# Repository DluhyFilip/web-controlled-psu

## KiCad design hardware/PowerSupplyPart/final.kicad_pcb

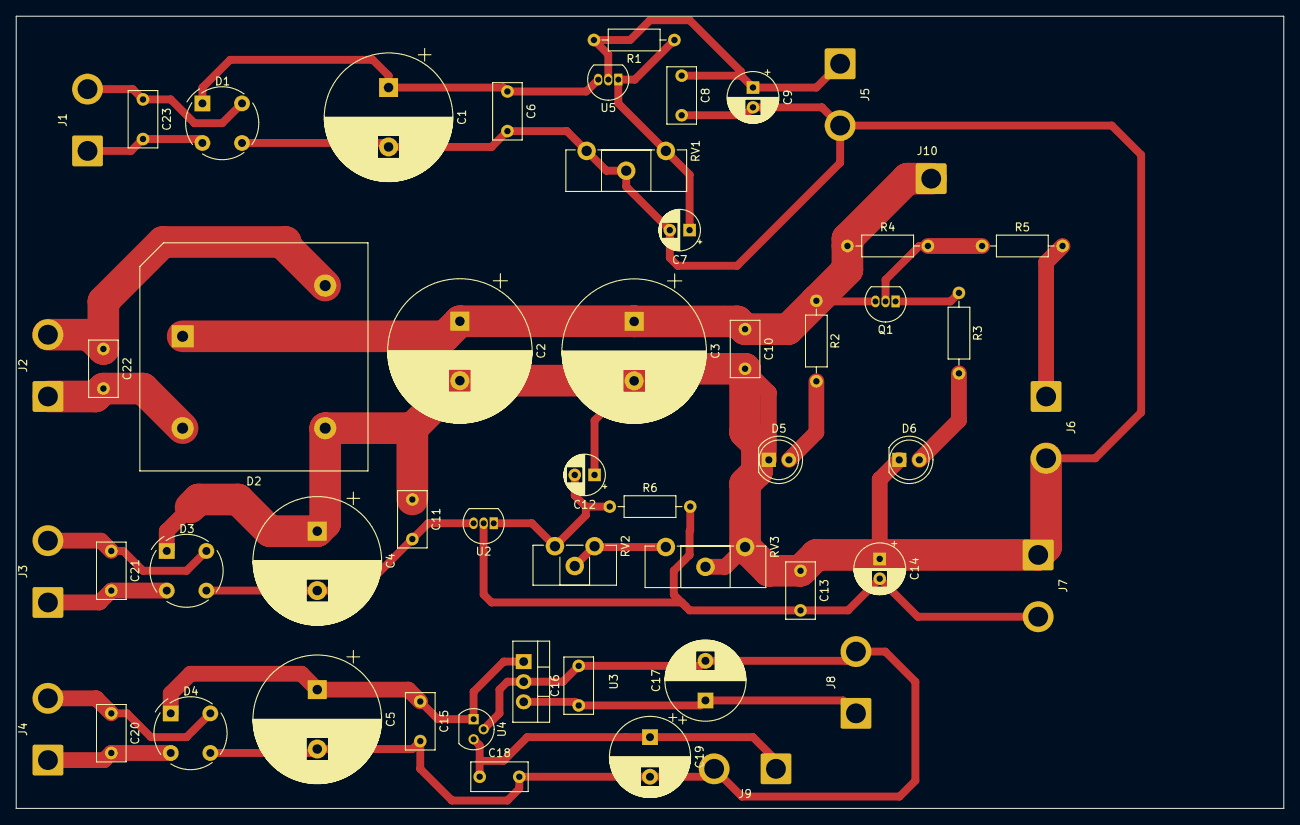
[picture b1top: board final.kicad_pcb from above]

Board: 2 copper layers, 160.0 x 100.0 mm, 53 parts (0 on the bottom side), 26 nets.

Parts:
C1, C4, C5: C_Polarized; CP_Radial_D16.0mm_P7.50mm
C2, C3: C_Polarized; CP_Radial_D18.0mm_P7.50mm
C6, C8, C10, C11, C13, C15, C16, C18, C20, C21, C22, C23: C; C_Rect_L7.0mm_W3.5mm_P5.00mm
C7: C; CP_Radial_D5.0mm_P2.50mm
C9, C14: C_Polarized; CP_Radial_D6.3mm_P2.50mm
C12: C_Polarized; CP_Radial_D5.0mm_P2.50mm
C17, C19: C_Polarized; CP_Radial_D10.0mm_P5.00mm
D1, D3, D4: D_Bridge_+A-A; Diode_Bridge_Round_D9.0mm
D2: D_Bridge_+A-A; Diode_Bridge_28.6x28.6x7.3mm_P18.0mm_P11.6mm
D5, D6: LED; LED_D5.0mm
J1, J2, J3, J4, J5, J6, J7, J8, J9: Conn_01x02_Socket; SolderWire-2sqmm_1x02_P7.8mm_D2mm_OD3.9mm
J10: Conn_01x01_Socket; SolderWire-2sqmm_1x01_D2mm_OD3.9mm
Q1: BC556; TO-92_Inline
R1, R2, R3, R4, R5, R6: R; R_Axial_DIN0207_L6.3mm_D2.5mm_P10.16mm_Horizontal
RV1, RV3: R_Potentiometer; Potentiometer_Piher_PT-15-H01_Horizontal
RV2: R_Potentiometer; Potentiometer_Piher_PT-10-H01_Horizontal
U2: LM337L_TO92; TO-92_Inline
U3: LM78M05_TO220; TO-220-3_Vertical
U4: L7805; TO-92
U5: LM317L_TO92; TO-92_Inline

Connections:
unnamed: C1.1, C6.1, D1.1 (+), U5.3 (VI)
unnamed: C1.2, C2.2, C3.2, C4.1, C6.2, C7.2, C8.2, C9.2, C10.2, C11.1, C12.1, C13.1, C14.1, D1.3 (-), D2.3 (-), D3.1 (+), D5.1 (K), D6.1 (K), J5.2, J6.2, J7.1, RV1.2, RV1.3, RV3.1, RV3.2
unnamed: C2.1, C3.1, C10.1, D2.1 (+), J10.1, Q1.3 (E), R2.1, R4.1
unnamed: C4.2, C11.2, D3.3 (-), U2.3 (VI)
unnamed: C5.1, C15.1, D4.1 (+), U3.1 (VI), U4.1 (IN)
unnamed: C5.2, C15.2, C16.2, C17.2, C18.2, C19.2, D4.3 (-), J8.2, J9.2, U3.2 (GND), U4.2 (GND)
unnamed: D5.2 (A), R2.2
unnamed: D6.2 (A), R3.2
unnamed: C23.2, D1.2, J1.1
unnamed: C23.1, D1.4, J1.2
unnamed: C22.2, D2.2, J2.1
unnamed: C22.1, D2.4, J2.2
unnamed: C21.2, D3.2, J3.1
unnamed: C21.1, D3.4, J3.2
unnamed: C20.2, D4.2, J4.1
unnamed: C20.1, D4.4, J4.2
unnamed: C8.1, C9.1, J5.1, R1.2, U5.2 (VO)
unnamed: J6.1, R5.2
unnamed: C13.2, C14.2, J7.2, R6.2, U2.2 (VO)
unnamed: C16.1, C17.1, J8.1, U3.3 (VO)
unnamed: C18.1, C19.1, J9.1, U4.3 (OUT)
unnamed: Q1.2 (B), R4.2, R5.1
unnamed: Q1.1 (C), R3.1
unnamed: RV2.1, RV2.2, RV3.3
unnamed: C12.2, R6.1, RV2.3, U2.1 (ADJ)
unnamed: C7.1, R1.1, RV1.1, U5.1 (ADJ)

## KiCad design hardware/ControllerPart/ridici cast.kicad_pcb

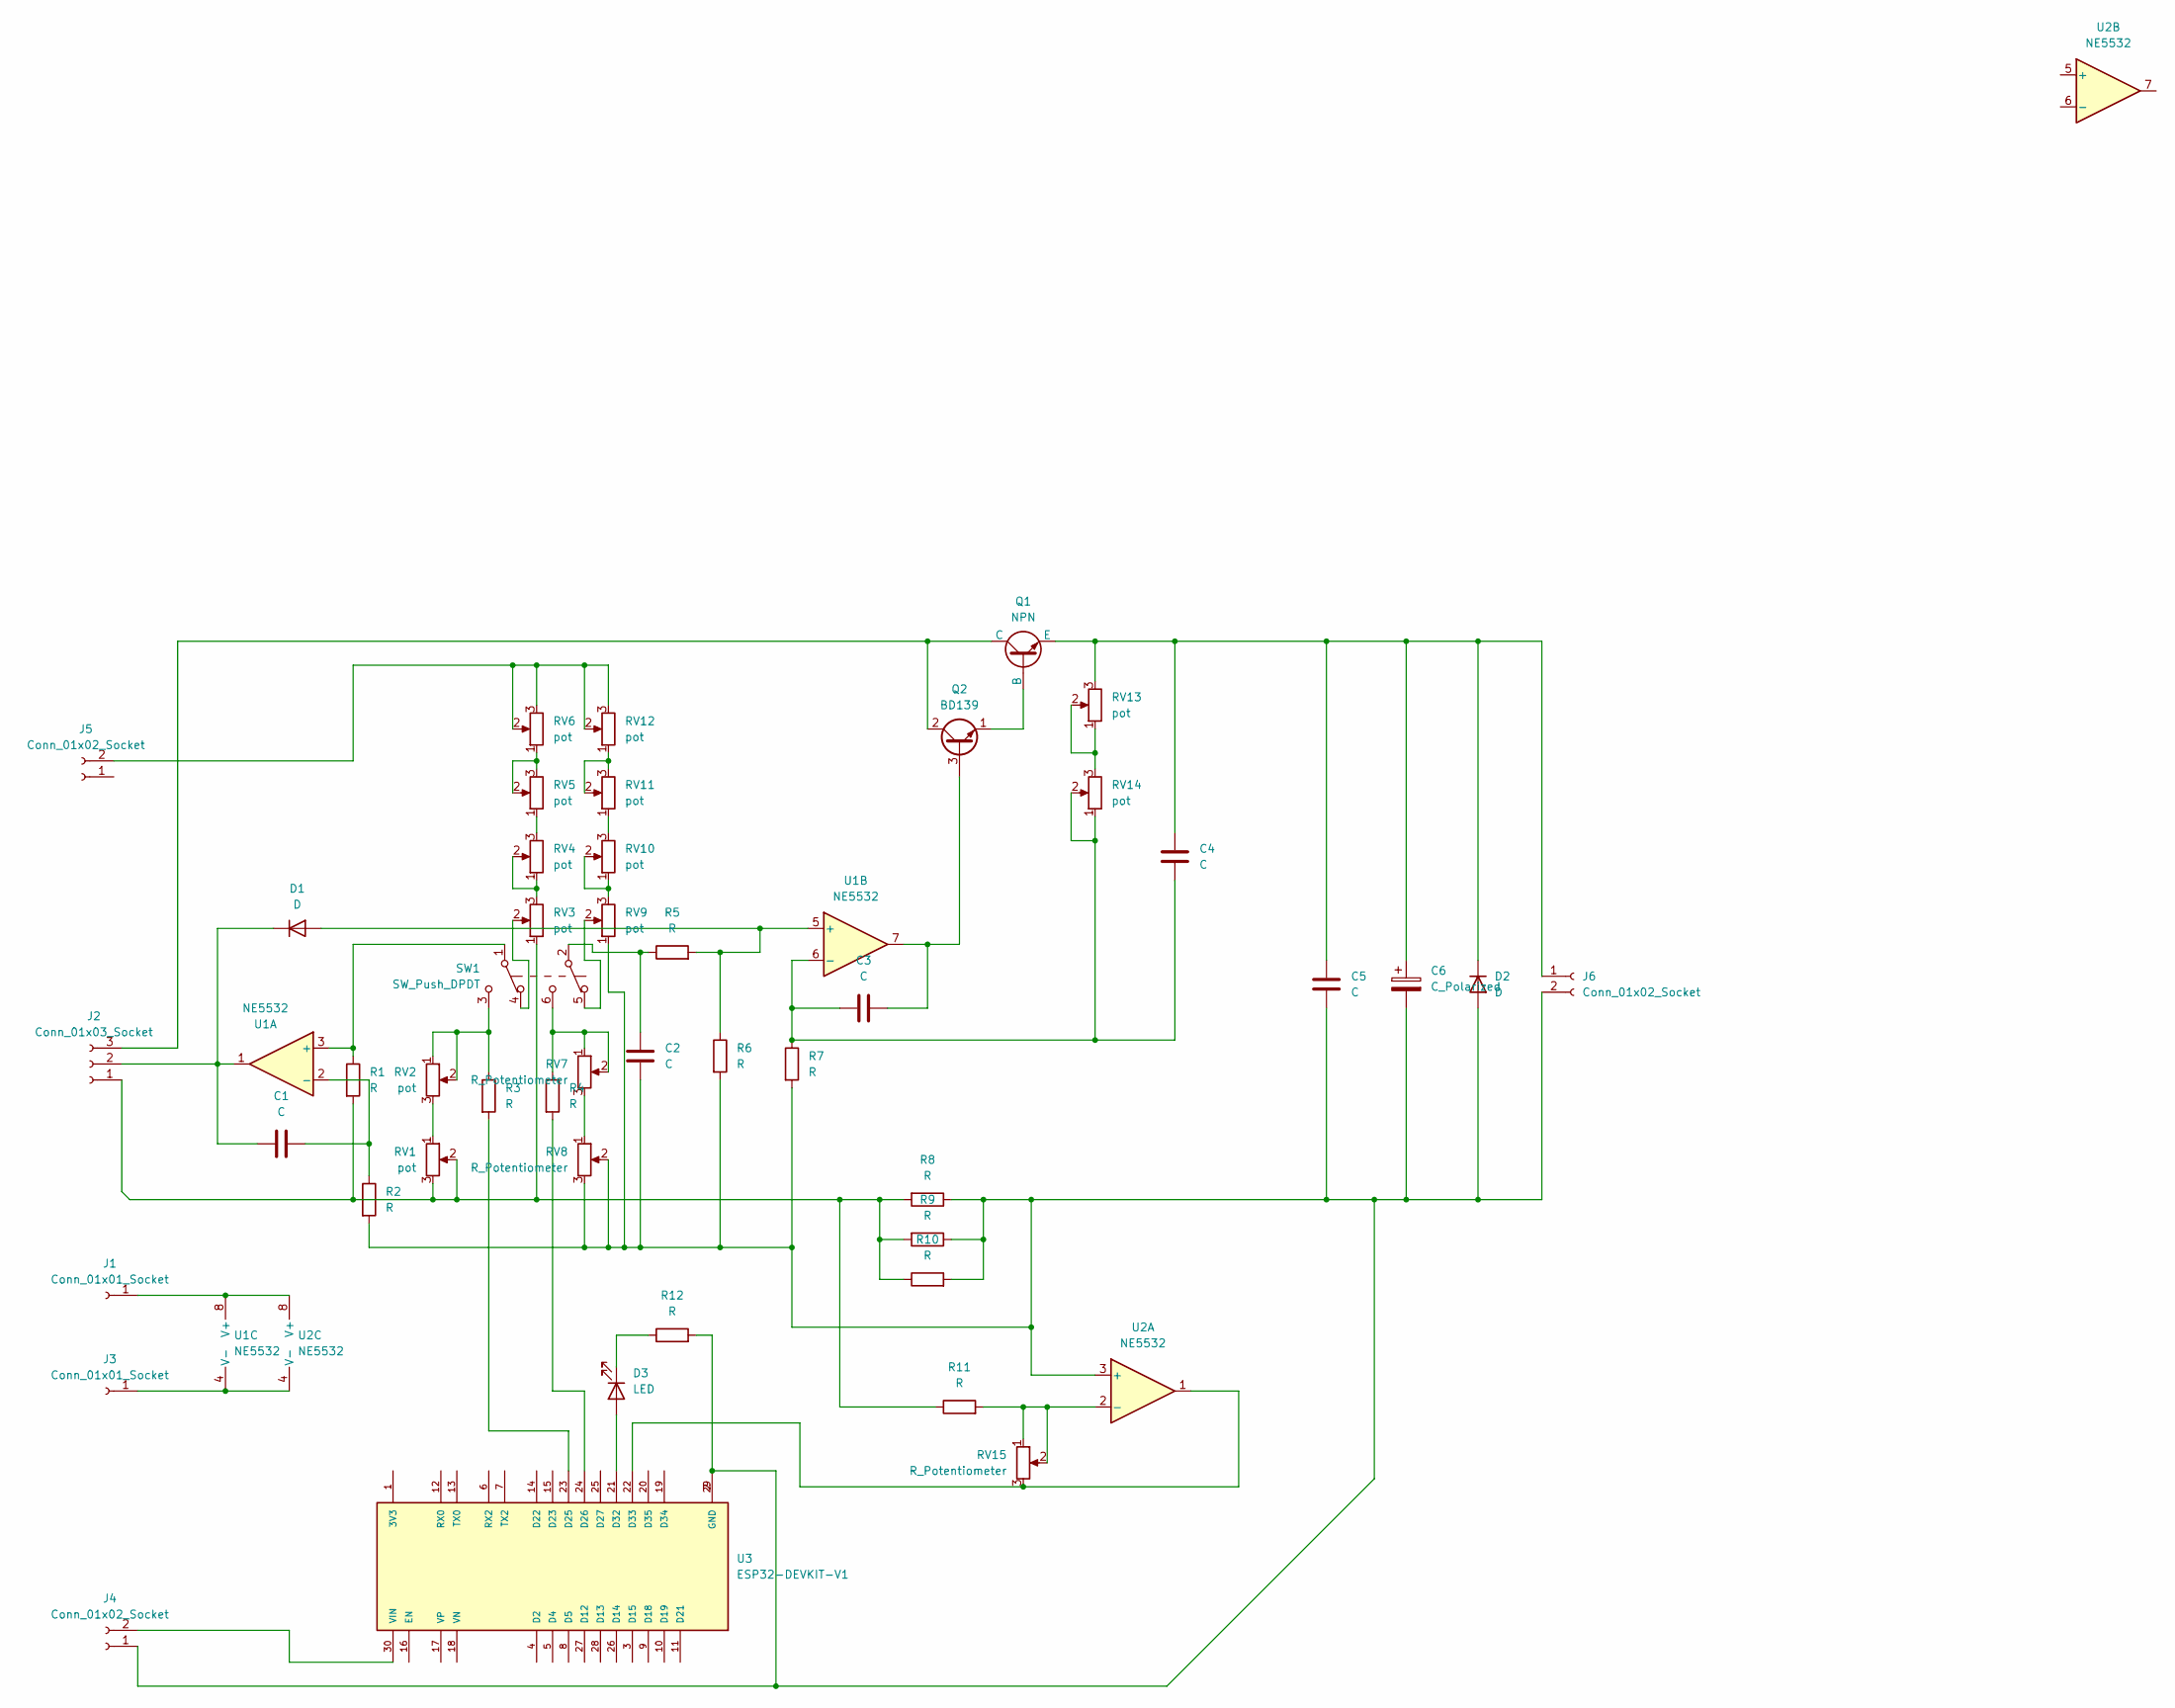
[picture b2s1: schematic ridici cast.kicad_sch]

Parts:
C1, C2, C3, C4, C5: C; C_Disc_D5.0mm_W2.5mm_P5.00mm
C6: C_Polarized; CP_Radial_D8.0mm_P2.50mm
D1, D2: D; D_DO-15_P12.70mm_Horizontal
D3: LED; LED_D5.0mm
J1, J3: Conn_01x01_Socket; SolderWire-2sqmm_1x01_D2mm_OD3.9mm
J2: Conn_01x03_Socket; SolderWire-2sqmm_1x03_P7.8mm_D2mm_OD3.9mm
J4, J5, J6: Conn_01x02_Socket; SolderWire-2sqmm_1x02_P7.8mm_D2mm_OD3.9mm
Q1: NPN; SolderWire-2sqmm_1x03_P7.8mm_D2mm_OD3.9mm
Q2: BD139; TO-126-3_Vertical
R1, R2, R3, R4, R5, R6, R7, R11, R12: R; R_Axial_DIN0204_L3.6mm_D1.6mm_P7.62mm_Horizontal
R8, R9, R10: R; R_Axial_Power_L48.0mm_W12.5mm_P55.88mm
RV1, RV2, RV6, RV11, RV12, RV14: pot; Potentiometer_Piher_PT-10-H01_Horizontal
RV3, RV4, RV9, RV10: pot; SolderWire-2sqmm_1x03_P7.8mm_D2mm_OD3.9mm
RV5, RV13: pot; Potentiometer_Piher_PT-15-H01_Horizontal
RV7, RV15: R_Potentiometer; Potentiometer_Piher_PT-10-H01_Horizontal
RV8: R_Potentiometer; Potentiometer_Piher_PT-15-H01_Horizontal
SW1: SW_Push_DPDT; SolderWire-2sqmm_1x06_P7.8mm_D2mm_OD3.9mm
U1, U2: NE5532; DIP-8_W7.62mm
U3: ESP32-DEVKIT-V1; MODULE_ESP32_DEVKIT_V1; PARTREV N/A

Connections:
unnamed: C2.1, R5.1, SW1.2 (B)
unnamed: D1.2 (A), R5.2, R6.1, U1.5 (+)
unnamed: C1.1, D1.1 (K), J2.2, U1.1
unnamed: C2.2, C5.2, C6.2, D2.2 (A), J4.1, J6.2, R2.2, R6.2, R7.2, R8.1, R9.1, R10.2, R12.2, RV8.2, RV8.3, RV9.1, U2.3 (+), U3.2 (GND), U3.29 (GND)
unnamed: C4.1, C5.1, C6.1, D2.1 (K), J6.1, Q1.3 (E), RV13.3
unnamed: D3.1 (K), R12.1
unnamed: J1.1, U1.8 (V+), U2.8 (V+)
unnamed: J2.1, R1.2, R8.2, R9.2, R10.1, R11.1, RV1.2, RV1.3, RV3.1
unnamed: J2.3, Q1.1 (C), Q2.2 (C)
unnamed: J3.1, U1.4 (V-), U2.4 (V-)
unnamed: J5.2, RV6.2, RV6.3, RV12.2, RV12.3
unnamed: Q1.2 (B), Q2.1 (E)
unnamed: C3.2, Q2.3 (B), U1.7
unnamed: R3.1, RV2.1, RV2.2, SW1.3 (C)
unnamed: R4.1, RV7.1, RV7.2, SW1.6 (C)
unnamed: RV1.1, RV2.3
unnamed: RV3.2, SW1.4 (A)
unnamed: RV3.3, RV4.1, RV4.2
unnamed: RV4.3, RV5.1
unnamed: RV5.2, RV5.3, RV6.1
unnamed: RV7.3, RV8.1
unnamed: RV9.2, SW1.5 (A)
unnamed: RV9.3, RV10.1, RV10.2
unnamed: RV10.3, RV11.1
unnamed: RV11.2, RV11.3, RV12.1
unnamed: RV13.1, RV13.2, RV14.3
unnamed: R1.1, SW1.1 (B), U1.3 (+)
unnamed: C1.2, R2.1, U1.2 (-)
unnamed: C3.1, C4.2, R7.1, RV14.1, RV14.2, U1.6 (-)
unnamed: R11.2, RV15.1, RV15.2, U2.2 (-)
unnamed: D3.2 (A), U3.21 (D32)
unnamed: RV15.3, U2.1, U3.22 (D33)
unnamed: R3.2, U3.23 (D25)
unnamed: R4.2, U3.24 (D26)
unnamed: J4.2, U3.30 (VIN)

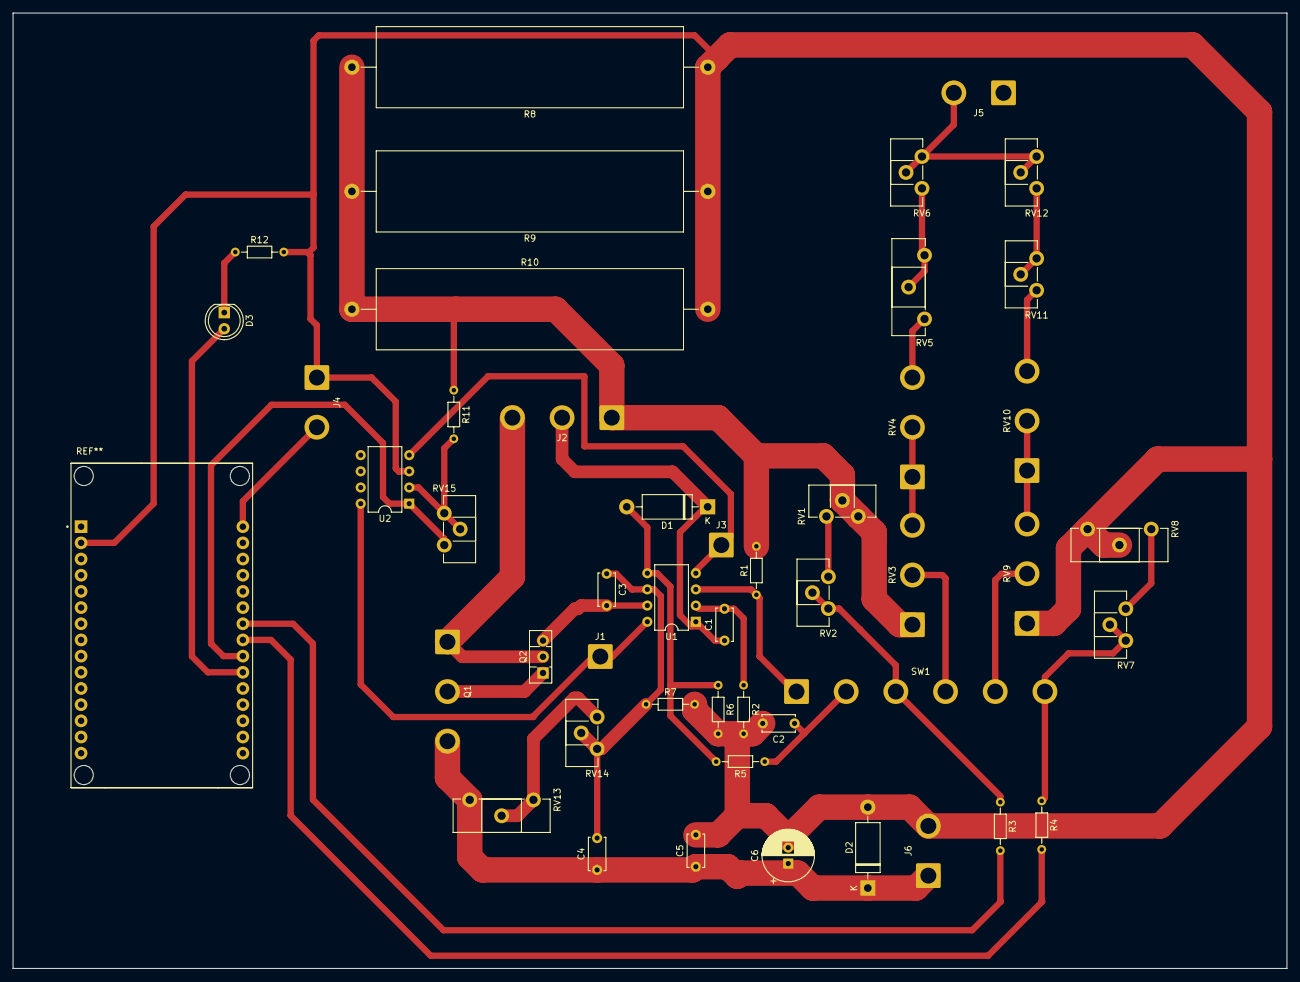
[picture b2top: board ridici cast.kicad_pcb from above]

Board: 2 copper layers, 200.0 x 150.0 mm, 47 parts (0 on the bottom side), 30 nets.

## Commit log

2026-03-10 adding documents and KiCad schematics
2026-03-10 deleting unwanted files and backups
